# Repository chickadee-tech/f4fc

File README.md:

# Chickadee Tech F4FC #
This an STM32F4-based flight control Polystack board for multirotors designed by Chickadee Tech. It features an STM32F405VGT6 microcontroller and an MPU-6000 accelerometer/gyroscope. It runs a modified version of [Betaflight](https://github.com/betaflight/betaflight) available [here](github.com/chickadee-tech/betaflight) with the CKD_F4FC target.

## Documentation ##
See the [wiki](https://github.com/chickadee-tech/f4fc/wiki) for documentation.

## Polystack ##
This **control** board is part of the Polystack platform for modular microcontrol systems. More information on the platform can be found at [polystack.org](http://polystack.org).

## Support ##
If you need support with a board you own or have development questions please email support@chickadee.tech or check [chickadee.tech/support](https://chickadee.tech/support) for other ways to get support.

## Contributing ##
Please note that this project is released with a [Contributor Code of Conduct](CODE_OF_CONDUCT.md). By participating in this project you agree to abide by its terms.

### Setup ###
Components and footprints for PCB parts are not included in this repository. Instead, checkout the [chickadee-tech/kicad-libs](https://github.com/chickadee-tech/kicad-libs) repository in the same directory that this repository is checked out in. All part definitions should be relative so that they will load correctly.

### Pull requests ###
For fixes please submit a pull request to the original repository. After the pull request is merged, check the [Chickadee Tech Active Contributor Discount (ACD)](https://chickadee.tech/active-contributor) to see if you are eligible for a discount code to use on your next purchase.

### Derivatives ###
If developing your own version of the F4FC please remove all Chickadee Tech trademarks and follow the [CC-BY license](LICENSE). While not required, please consider open sourcing your modifications so others can learn from your improvements. If you do email support@chickadee.tech and we may choose to add your project to the ACD.

You may also license the Polystack logo for free by emailing support@chickadee.tech. We'll ask for your gerbers to ensure the design complies with specifications laid out [here](https://github.com/chickadee-tech/polystack/wiki) and provide written permission to use the trademark after compliance has been demonstrated.

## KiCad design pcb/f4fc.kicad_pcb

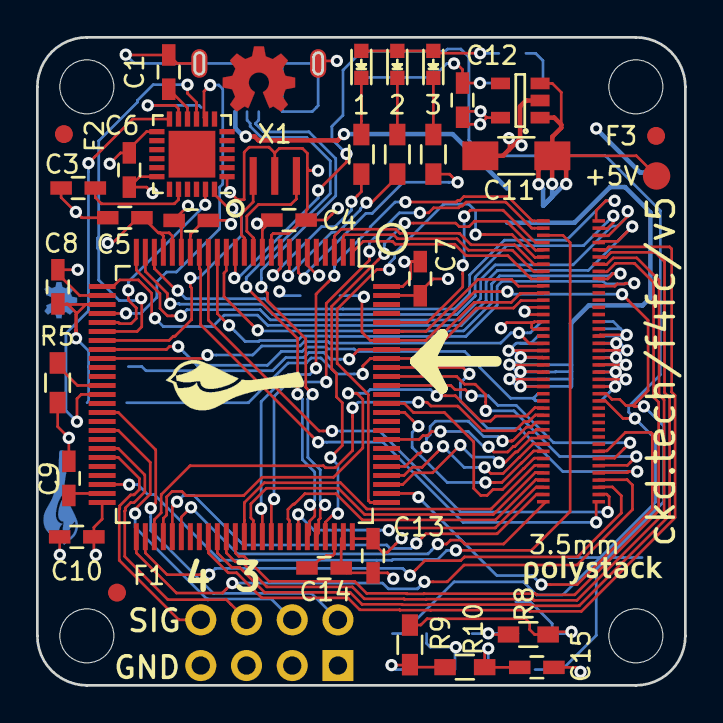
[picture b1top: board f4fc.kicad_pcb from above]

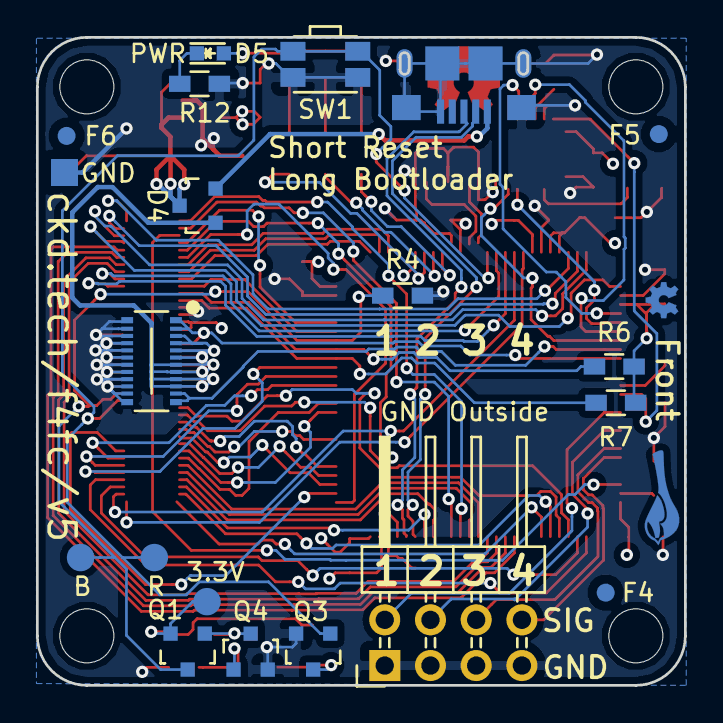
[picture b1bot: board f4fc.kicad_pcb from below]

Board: 4 copper layers, 36.0 x 36.0 mm, 55 parts (20 on the bottom side), 81 nets.

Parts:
C1, C4, C6, C7, C8, C10, C13: 0.1uF; C_0603_HandSoldering
C2: 4.7uF; C_0603_HandSoldering
C3: 2.2nF; C_0603_HandSoldering
C5: 1uF; C_0603_HandSoldering
C9, C14, C15: 2.2uF; C_0603_HandSoldering
C11: 10uF+; C_1206_HandSoldering
C12: 1uF+; C_0603_HandSoldering
D1: Green; LED_0603
D2: Yellow; LED_0603
D3, D5: Red; LED_0603
D4: D_Schottky_x2_KCom_AAK; SOT-23
F1, F2, F3, F4, F5, F6: 1mm; Fiducial
P1: 3V3; Measurement_Point_Round-SMD-Pad_Small
P2: CONN_01X01; Measurement_Point_Square-SMD-Pad_Small
P3: USB_OTG; Mini-USB-B-EDGE
P4: CONN_02X04; Pin_Header_Angled_2x04
P5: CONN_02X10; DF40-20pin-Header
P6: RESET; Measurement_Point_Round-SMD-Pad_Small
P7: BOOT0; Measurement_Point_Round-SMD-Pad_Small
P9: 5V; Measurement_Point_Round-SMD-Pad_Small
PORT_OUT1: CKD_SANDWICH; DF40-3-4mm-80pin-Receptacle
Q1: Q_PMOS_GSD; SOT-23
Q3, Q4: Q_NMOS_GSD; SOT-23
R1, R2, R3, R12: 1k; R_0603_HandSoldering
R4, R5, R8: 10k; R_0603_HandSoldering
R6, R7: 4.7k; R_0603_HandSoldering
R9: 470k; R_0603_HandSoldering
R10: 100k; R_0603_HandSoldering
SW1: SW_PUSH; SW_SPST_EVQP7A
U1: MPU-6000; QFN-24-1EP_4x4mm_Pitch0.5mm
U2: STM32F40xxx; LQFP-100_14x14mm_Pitch0.5mm
U3: TLV70233DBV; SOT-23-5
X1: 8mhz; CSTCE_G-CSTCE_G_Z
svg2mod: G***; polystack-bold-0.4

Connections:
+5V: D4.1, P5.3, P5.5, P5.7, P5.9, P5.11, P5.13, P5.15, P5.17, PORT_OUT1.19, PORT_OUT1.20, PORT_OUT1.21, PORT_OUT1.22, PORT_OUT1.23, PORT_OUT1.24
+5VA: D4.2, P3.1
+BATT: P5.19, PORT_OUT1.18, U2.34
/ADC1: PORT_OUT1.49, U2.15
/ADC2: PORT_OUT1.50, U2.16
/GPIO1_14_SWCLK: PORT_OUT1.6, U2.76
/GPIO2_13_SWDIO: PORT_OUT1.5, U2.72
/GPIO3: PORT_OUT1.7, U2.3
/GPIO4: PORT_OUT1.8, U2.2
/GPIO5: PORT_OUT1.9, U2.1
/GPIO6: PORT_OUT1.10, U2.95
/LED0: R3.1, U2.7
/LED1: R2.1, U2.8
/LED2: R1.1, U2.9
/MPU_INT: U1.12, U2.38
/MPU_MISO: U1.9, U2.31
/MPU_MOSI: U1.24, U2.32
/MPU_NSS: U1.8, U2.29
/MPU_SCK: U1.23, U2.30
/Power/CURRENT: P5.1, U2.33
/Reset/BOOT0: P7.1, PORT_OUT1.65, Q1.3, R4.2, U2.94
/Reset/RESET: P6.1, PORT_OUT1.66, Q3.1, SW1.2, U2.14
/SPI1_MISO: PORT_OUT1.79, U2.17
/SPI1_MOSI: PORT_OUT1.80, U2.18
/SPI1_NSS: PORT_OUT1.77, U2.51
/SPI1_SCK: PORT_OUT1.78, U2.52
/SPI2_MISO: PORT_OUT1.75, U2.90
/SPI2_MOSI: PORT_OUT1.76, U2.91
/SPI2_NSS: PORT_OUT1.73, U2.77
/SPI2_SCK: PORT_OUT1.74, U2.89
/TIM1_CH1: P4.2, U2.40
/TIM1_CH2: P4.4, U2.42
/TIM1_CH3: P4.6, U2.44
/TIM1_CH4: P4.8, U2.45
/TIM2_CH4: PORT_OUT1.3, U2.48
/TIM3_CH4: PORT_OUT1.2, U2.66
/TIM8_CH3: PORT_OUT1.1, U2.65
/TIM11_CH1: PORT_OUT1.4, U2.96
/TIM12_CH1_UART8_RX: PORT_OUT1.28, U2.53
/TIM12_CH2_UART8_TX: PORT_OUT1.27, U2.54
/TIMG1_CH1: PORT_OUT1.41, U2.23
/TIMG1_CH2: PORT_OUT1.42, U2.24
/TIMG1_CH3: PORT_OUT1.43, U2.25
/TIMG1_CH4: PORT_OUT1.44, U2.26
/TIMG2_CH1: PORT_OUT1.45, U2.59
/TIMG2_CH2: PORT_OUT1.46, U2.60
/TIMG2_CH3: PORT_OUT1.47, U2.61
/TIMG2_CH4: PORT_OUT1.48, U2.62
/UART1_RX: PORT_OUT1.38, U2.69
/UART1_TX: PORT_OUT1.37, U2.68
/UART2_RX: PORT_OUT1.34, U2.87
/UART2_TX: PORT_OUT1.33, U2.86
/UART3_RX: PORT_OUT1.40, U2.56
/UART3_TX: PORT_OUT1.39, U2.55
/UART4_RX: PORT_OUT1.32, U2.79
/UART4_TX: PORT_OUT1.31, U2.78
/UART5_RX: PORT_OUT1.30, U2.83
/UART5_TX: PORT_OUT1.29, U2.80
/UART6_RX: PORT_OUT1.36, U2.64
/UART6_TX: PORT_OUT1.35, U2.63
/USB_D+: P3.3, U2.71
/USB_D-: P3.2, U2.70
/i2c_SCL: PORT_OUT1.12, R7.2, U2.92
/i2c_SDA: PORT_OUT1.11, R6.1, U2.93
GNDPWR: C1.2, C2.1, C3.1, C4.1, C5.1, C6.2, C7.1, C8.1, C9.2, C10.2, C11.2, C12.2, C13.1, C14.1, C15.2, P2.1, P3.5, P3.6, P4.1, P4.3, P4.5, P4.7, P5.2, P5.4, P5.6, P5.8, P5.10, P5.12, P5.14, P5.16, P5.18, P5.20, PORT_OUT1.13, PORT_OUT1.14, PORT_OUT1.57, PORT_OUT1.58, PORT_OUT1.59, PORT_OUT1.60, PORT_OUT1.61, PORT_OUT1.62, PORT_OUT1.63, PORT_OUT1.64, Q3.2, Q4.2, R4.1, R5.2, R12.2, SW1.1, U1.1, U1.11, U1.18, U2.10, U2.20, U2.27, U2.74, U2.99, U3.2, X1.3
unnamed: C1.1, U1.10
unnamed: C3.2, U1.20
unnamed: C9.1, U2.49
unnamed: C11.1, D4.3, P9.1, U3.1, U3.3
unnamed: C14.2, U2.73
unnamed: C15.1, Q4.1, R10.1
unnamed: D1.1, R1.2
unnamed: D2.1, R2.2
unnamed: D3.1, R3.2
unnamed: D5.1, R12.1
unnamed: Q1.1, Q4.3, R8.2
unnamed: Q3.3, R9.2, R10.2
unnamed: R5.1, U2.37
unnamed: U2.12, X1.1
unnamed: U2.13, X1.2
VDD: C2.2, C4.2, C5.2, C6.1, C7.2, C8.2, C10.1, C12.1, C13.2, D1.2, D2.2, D3.2, D5.2, P1.1, PORT_OUT1.15, PORT_OUT1.16, Q1.2, R6.2, R7.1, R8.1, R9.1, U1.13, U2.6, U2.11, U2.19, U2.21, U2.22, U2.28, U2.50, U2.75, U2.100, U3.5

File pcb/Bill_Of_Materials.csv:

part name,symbol,size (imp),max current,unit price,units per build,units in stock,On Order,order total,Manufacturer ID,source url,MacroFab HP,datasheet,datasheet2,,
C 0.1uF,"C1, C4, C6, C7, C8, C10, C13",603,,$0.02,7,400,SMD Binder - Capacitors,$0.15,C0603C104K4RACTU,http://www.digikey.com/product-detail/en/C0603C104K4RACTU/39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,,MF-CAP-0603-0.1uF,http://www.kemet.com/docfinder?Partnumber=C0603C104K4RACTU,,
C 4.7uF,C2,,,$0.05,1,8,SMD Binder - Capacitors,$0.05,C0603C475K9PACTU,http://www.digikey.com/product-detail/en/C0603C475K9PACTU/39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,http://www.mouser.com/ProductDetail/Kemet/C0603C475K9PACTU/?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,N,,,
C 2.2nF (2200pF) X7R 50V,C3,603,,$0.01,1,94,SMD Binder - Capacitors,$0.01,C0603C222K5RACTU,http://www.digikey.com/product-detail/en/C0603C222K5RACTU/39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,http://www.mouser.com/ProductDetail/Kemet/C0603C222K5RACTU/?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,N,,,
C 2.2uF,"C9, C14, C15",603,,$0.05,3,92,SMD Binder - Capacitors,$0.14,C0603C225K9PACTU,http://www.digikey.com/product-detail/en/C0603C225K9PACTU/39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,http://www.mouser.com/ProductDetail/Kemet/C0603C225K9PACTU/?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,,,,
C 1uF X7R,"C5, C12",603,,$0.03,2,20,SMD Binder - Capacitors,$0.06,TMK107B7105KA-T,http://www.digikey.com/product-detail/en/TMK107B7105KA-T/587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,,MF-CAP-0603-1uF,http://ds.yuden.co.jp/TYCOMPAS/ut/detail.do?productNo=TMK107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,,
C 10uF X5R,C11,1206,,$0.24,1,80,SMD Binder - Capacitors,$0.24,C3216X5R1C106M160AA,http://www.digikey.com/product-detail/en/C3216X5R1C106M160AA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,,MF-CAP-1206-10uF,http://product.tdk.com/en/catalog/datasheets/mlcc_commercial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,,
red led,"D3, D5",,,$0.19,2,71,SMD Binder - Diodes,$0.37,LTST-C190KRKT,http://www.digikey.com/product-detail/en/LTST-C190KRKT/160-1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,,MF-LED-0603-RED,http://optoelectronics.liteon.com/upload/download/DS-22-99-0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,,
yellow led,D2,,,$0.20,1,87,SMD Binder - Diodes,$0.20,LTST-C190KSKT,http://www.digikey.com/product-detail/en/LTST-C190KSKT/160-1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,,N,http://optoelectronics.liteon.com/upload/download/DS-22-99-0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,,
green led,D1,,,$0.19,1,83,SMD Binder - Diodes,$0.19,LTST-C190KGKT,http://www.digikey.com/product-detail/en/LTST-C190KGKT/160-1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,,Y,http://optoelectronics.liteon.com/upload/download/DS22-2000-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,,
Power OR Diode,D4,,500mA,$0.49,1,6,SMD Binder - Diodes,$0.49,"PMEG2005CT,215","http://www.digikey.com/product-detail/en/PMEG2005CT,215/568-6500-1-ND/2531787",http://www.mouser.com/ProductDetail/NXP/PMEG2005CT215/?qs=%2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,N,http://www.nxp.com/documents/data_sheet/PMEG2005CT.pdf,,
~3.5mm Spacer,Off Board,,,$0.08,4,81,SMD Binder - Connectors,$0.33,908-140,http://www.mouser.com/search/ProductDetail.aspx?R=0virtualke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,,N,,,
Nylon Hex Nut,Off Board,,,$0.10,8,94,SMD Binder - Connectors,$0.76,4688,http://www.mouser.com/ProductDetail/Keystone-Electronics/468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,,N,,,
usb otg,P3,,500mA,$0.46,1,7,SMD Binder - Connectors,$0.46,10118193-0001LF,http://www.digikey.com/product-detail/en/10118193-0001LF/609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,http://www.mouser.com/ProductDetail/FCI/10118193-0001LF/?qs=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,MF-CON-MICROUSB-RIGHT,,,
2x4 right angle,P4,,,$0.80,1,2,SMD Binder - Connectors,$0.80,5-102975-4,,http://www.mouser.com/ProductDetail/TE-Connectivity-AMP/5-10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,N,,,
80 pin receptacle (3.5mm),CKD_SANDWICH,,0.3A a pin,$2.42,1,1,SMD Binder - Connectors,$2.42,DF40HC(3.5)-80DS-0.4V(51),http://www.digikey.com/product-detail/en/DF40HC(3.5)-80DS-0.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,http://www.mouser.com/ProductDetail/Hirose-Electric/DF40HC35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,N,http://www.hirose.co.jp/cataloge_hp/ed_DF40_20140305.pdf,,
20pin hirose header,P5,,0.3A a pin,$0.79,1,7,SMD Binder - Connectors,$0.79,DF40C-20DP-0.4V(51),http://www.digikey.com/product-detail/en/DF40C-20DP-0.4V(51)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,http://www.mouser.com/ProductDetail/Hirose-Electric/DF40C-20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,N,http://www.hirose.co.jp/cataloge_hp/ed_DF40_20140305.pdf,,
Chickadee F4FC v1,PCB,,,$6.73,1,3,PCB,$6.73,CKD-F4FC-V1,,,N,,,
p-channel mosfet,Q1,"TO-236-3, SC-59, SOT-23-4",220mA continuous,$0.10,1,97,SMD Binder - ICs,$0.10,BSS84,http://www.digikey.com/product-detail/en/fairchild-semicondu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,http://www.mouser.com/search/ProductDetail.aspx?R=0virtualke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,MF-DSC-SOT233-BSS84,https://www.fairchildsemi.com/datasheets/BS/BSS84.pdf,,
n-channel mosfet,"Q3, Q4","TO-236-3, SC-59, SOT-23-3",220mA continuous,$0.09,2,59,SMD Binder - ICs,$0.19,BSS138,http://www.digikey.com/product-detail/en/BSS138/BSS138CT-ND/244294,,MF-DSC-SOT233-BSS138,https://www.fairchildsemi.com/datasheets/BS/BSS138.pdf,,
R 1k,"R1, R2, R3, R12",603,,$0.01,4,993,SMD Binder - Resistors,$0.04,RC0603FR-071KL,http://www.digikey.com/product-detail/en/RC0603FR-071KL/311-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,,MF-RES-0603-1K,http://www.yageo.com/NewPortal/yageodocoutput?fileName=/pdf/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,,
R 10k,"R4, R5, R8",603,,$0.01,3,979,SMD Binder - Resistors,$0.03,RC0603FR-0710KL,http://www.digikey.com/product-detail/en/RC0603FR-0710KL/311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,,MF-RES-0603-10K,http://www.yageo.com/NewPortal/yageodocoutput?fileName=/pdf/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,,
R 4.7k,"R6, R7",1206,,$0.01,2,68,SMD Binder - Resistors,$0.01,RC0603FR-074K7L,http://www.digikey.com/product-detail/en/RC0603FR-074K7L/311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,,MF-RES-0603-5.6K,http://www.yageo.com/NewPortal/yageodocoutput?fileName=/pdf/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,,
R 470k,R9,603,,$0.01,1,68,SMD Binder - Resistors,$0.01,RC0603FR-07470KL,http://www.digikey.com/product-detail/en/RC0603FR-07470KL/31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,,MF-RES-0603-470K,http://www.yageo.com/NewPortal/yageodocoutput?fileName=/pdf/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,,
R 100k,R10,603,,$0.01,1,55,SMD Binder - Resistors,$0.01,RC0603FR-07100KL,http://www.digikey.com/product-detail/en/RC0603FR-07100KL/31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,,MF-RES-0603-100K,http://www.yageo.com/NewPortal/yageodocoutput?fileName=/pdf/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,,
reset- side switch,SW1,EVQ-P7A,,$0.69,1,7,SMD Binder - Misc,$0.69,EVQ-P7A01P,http://www.digikey.com/product-detail/en/EVQ-P7A01P/P16763CT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,http://www.mouser.com/ProductDetail/Panasonic/EVQ-P7A01P/?qs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,N,"http://media.digikey.com/pdf/Data%20Sheets/Panasonic%20Elect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,3,9P7).pdf",,
acc/gyro,U1,24pin QFN 4x4,,$10.72,1,4,SMD Binder - ICs,$10.72,MPU-6000,http://www.digikey.com/product-detail/en/MPU-6000/1428-1005-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,,N,http://store.invensense.com/datasheets/invensense/MPU-6050_D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,,
STM32F405,U2,100LQFP,,$10.63,1,2,SMD Binder - ICs,$10.63,STM32F405VGT6,http://www.digikey.com/product-detail/en/STM32F405VGT6/497-1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,http://www.mouser.com/ProductDetail/STMicroelectronics/STM32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,N,http://www.st.com/web/en/resource/technical/document/datashe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,Total Price,$37.81
3.3v regulator,U3,SOT23-5,0.3A,$0.49,1,8,SMD Binder - ICs,$0.49,TLV70233DBVR,http://www.digikey.com/product-detail/en/TLV70233DBVR/296-32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,http://www.mouser.com/ProductDetail/Texas-Instruments/TLV702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,MF-REG-SOT235-3.3V-300mA,http://www.ti.com/lit/ds/symlink/tlv702.pdf,,
8mhz resonator,X1,,,$0.38,1,8,SMD Binder - Misc,$0.38,CSTCE8M00G55-R0,https://www.digikey.com/product-detail/en/CSTCE8M00G55-R0/49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,http://www.mouser.com/ProductDetail/Murata/CSTCE8M00G55-R0/?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,N,http://www.murata.com/~/media/webrenewal/support/library/cat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,,
1x2 housing,Off Board,,,$0.08,4,48,SMD Binder - Connectors,$0.31,M20-1060200,http://www.digikey.com/product-detail/en/M20-1060200/952-222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,http://www.mouser.com/ProductDetail/Harwin/M20-1060200/?qs=%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,N,,,

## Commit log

2016-02-02 v1 of F4FC. Similar layout to F3FC but with an F4 chip. It has a higher clock speed and one more UART.
2016-03-05 F4FC v2 featuring corrected reset circuit.
    Other changes:
    * Route USB as differential pair.
    * Add fiducials
    * Remove copper pour from power connector
    * New reset circuit
    * Match up led nubmering to references
2016-03-23 Remove g2l and g3l layers. OSH Park support g2 and g3 now.
2016-04-07 More changes to F4. Can't remember what.
2016-04-13 Rebrand everything to Polystack and increment versions.
2016-04-16 Final gerbers for test manufacturing run.
2016-06-07 Update polystack logo to bold variant and bump version number.
2016-07-07 Add license information to many files. PCB design files are CC-BY and code is MIT license.
2016-07-07 Add back .gitignore after repo split.
2016-07-07 Convert to relative component and footprint paths.
